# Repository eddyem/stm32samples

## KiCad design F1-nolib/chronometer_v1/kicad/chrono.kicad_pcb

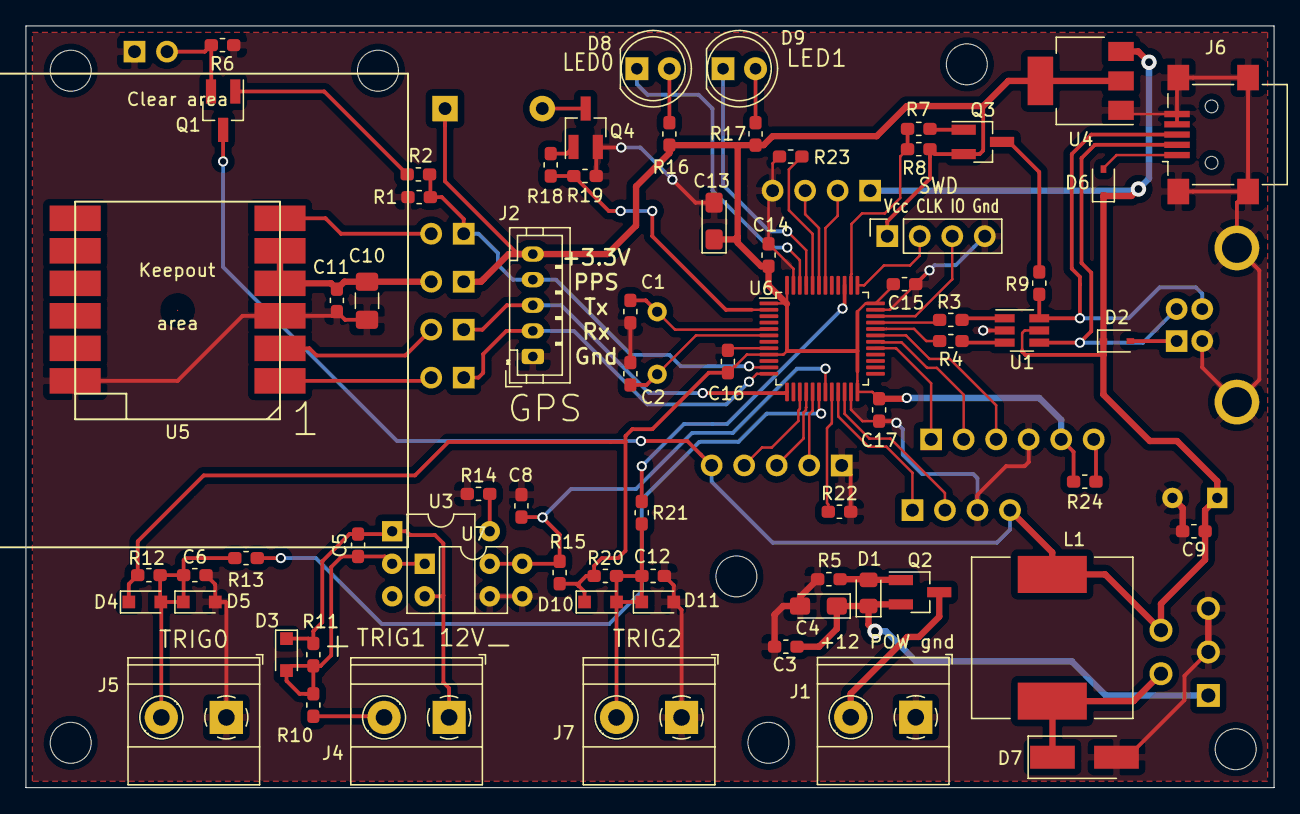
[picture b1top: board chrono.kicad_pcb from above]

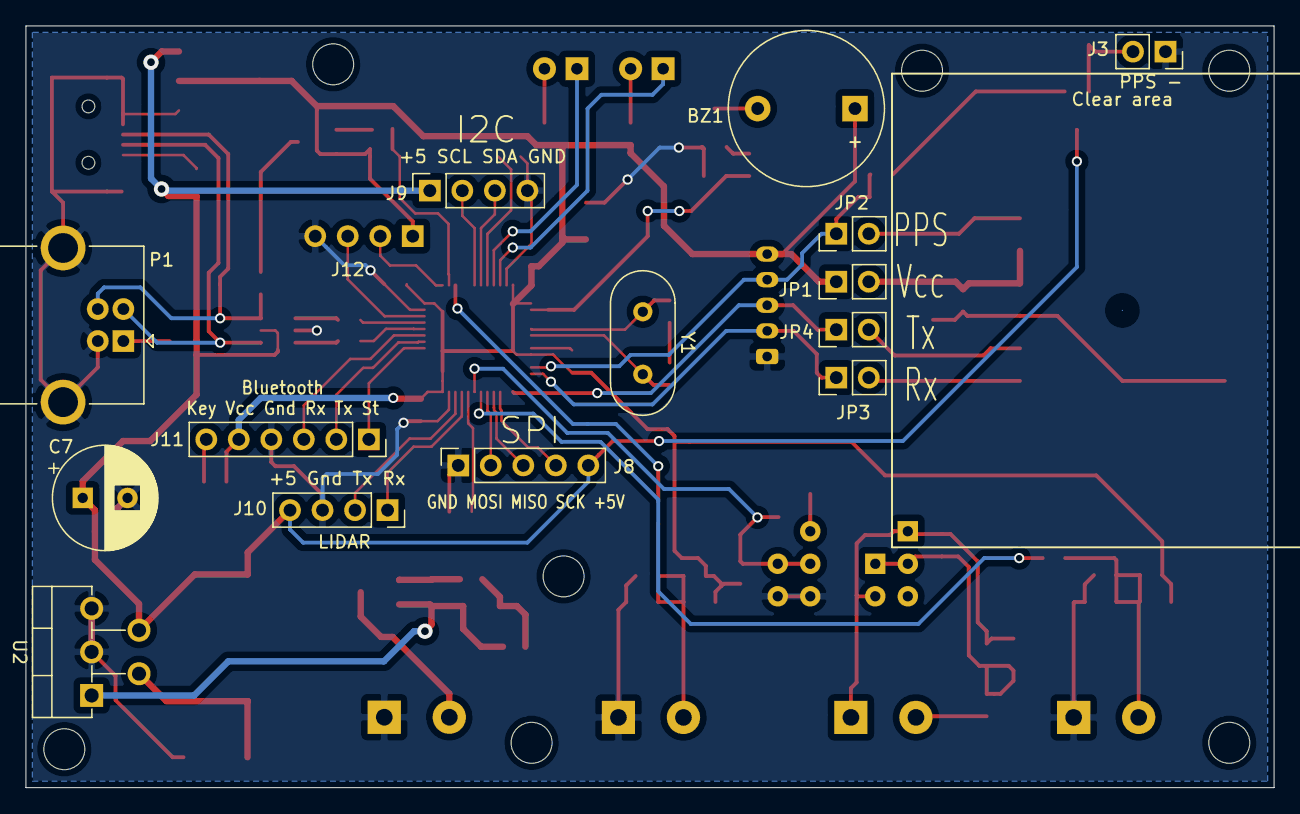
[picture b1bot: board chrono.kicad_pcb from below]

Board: 2 copper layers, 97.5 x 59.5 mm, 83 parts (14 on the bottom side), 60 nets.

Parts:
BZ1: Buzzer 3v3; Buzzer_12x9.5RM7.6
C1, C2: 12; C_0603_1608Metric_Pad1.05x0.95mm_HandSolder
C3, C5, C6, C8, C9, C11, C12, C14, C15, C16, C17: 0.1; C_0603_1608Metric_Pad1.05x0.95mm_HandSolder
C4, C13: 47u; CP_EIA-3216-18_Kemet-A_Pad1.58x1.35mm_HandSolder
C7: 100u; CP_Radial_D8.0mm_P3.50mm
C10: 10u; C_1206_3216Metric_Pad1.42x1.75mm_HandSolder
D1: MM3Z7V5; D_0805_2012Metric_Pad1.15x1.40mm_HandSolder
D2, D6: IN5819; D_SOD-323
D3, D4, D5, D10, D11: 1N5819; D_SOD-323_HandSoldering
D7: B340A; D_SMA_Handsoldering
D8: LED0; LED_D5.0mm
D9: LED1; LED_D5.0mm
J1: Power 12V; TerminalBlock_Phoenix_MKDS-1,5-2-5.08_1x02_P5.08mm_Horizont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
J2: GPS_ext; JST_PH_B5B-PH-K_1x05_P2.00mm_Vertical
J3: PPS; PinSocket_1x02_P2.54mm_Vertical
J4: Ext_trig1; TerminalBlock_Phoenix_MKDS-1,5-2-5.08_1x02_P5.08mm_Horizont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
J5: Ext_trig0; TerminalBlock_Phoenix_MKDS-1,5-2-5.08_1x02_P5.08mm_Horizont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
J6: USB_B_Mini; USB_Mini-B_Lumberg_2486_01_Horizontal
J7: Ext_trig2; TerminalBlock_Phoenix_MKDS-1,5-2-5.08_1x02_P5.08mm_Horizont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
J8: SPI; PinSocket_1x05_P2.54mm_Vertical
J9: I2C1; PinSocket_1x04_P2.54mm_Vertical
J10: LIDAR; PinSocket_1x04_P2.54mm_Vertical
J11: Bluetooth; PinSocket_1x06_P2.54mm_Vertical
J12: SWD; PinSocket_1x04_P2.54mm_Vertical
JP1, JP2, JP3, JP4: Jumper; PinHeader_1x02_P2.54mm_Vertical
L1: 100u; L_12x12mm_H4.5mm
P1: USB_B; USB_B_OST_USB-B1HSxx_Horizontal
Q1: MMBTA42; SOT-23_Handsoldering
Q2: AO3407; SOT-23_Handsoldering
Q3: SI2305; SOT-23_Handsoldering
Q4: IRML2502; SOT-23_Handsoldering
R1, R5, R8, R19, R23: 10k; R_0603_1608Metric_Pad1.05x0.95mm_HandSolder
R2: 2k2; R_0603_1608Metric_Pad1.05x0.95mm_HandSolder
R3, R4: 22; R_0603_1608Metric_Pad1.05x0.95mm_HandSolder
R6, R10, R11, R12, R20: 1k; R_0603_1608Metric_Pad1.05x0.95mm_HandSolder
R7, R18: 510; R_0603_1608Metric_Pad1.05x0.95mm_HandSolder
R9: 1k5; R_0603_1608Metric_Pad1.05x0.95mm_HandSolder
R13, R21: 100; R_0603_1608Metric_Pad1.05x0.95mm_HandSolder
R14, R24: 47k; R_0603_1608Metric_Pad1.05x0.95mm_HandSolder
R15, R16, R17: 220; R_0603_1608Metric_Pad1.05x0.95mm_HandSolder
R22: 100k; R_0603_1608Metric_Pad1.05x0.95mm_HandSolder
U1: USBLC6-2SC6; SOT-23-6_Handsoldering
U2: LM2576-5.0; TO-220-5_P3.4x3.7mm_StaggerEven_Lead3.8mm_Vertical
U3: 4N25; DIP-6_W7.62mm
U4: LM1117-3.3; SOT-223
U5: L80-R
U6: STM32F103C6Tx; LQFP-48_7x7mm_P0.5mm
U7: PC817; DIP-4_W7.62mm
Y1: 8MHz; Crystal_HC49-U_Vertical

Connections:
+3V3: BZ1.1, C13.1, C14.2, C15.2, C16.2, C17.2, D4.1, D10.1, J2.5, J11.5, J12.1, JP1.1, Q3.2, R8.2, R12.2, R15.1, R16.2, R17.2, R20.2, R24.1, U4.2, U4.4, U6.1, U6.9, U6.24, U6.36, U6.48
+5V: C7.1, C9.1, D2.1, D6.1, J8.5, J9.1, J10.4, L1.1, Q1.3, U1.5, U2.4, U4.3
/DM: J6.2, P1.2, U1.4
/DP: J6.3, P1.3, R9.2, U1.6
/LED0: D8.1, U6.46
/LED1: D9.1, U6.45
/MISO: J8.3, U6.16
/MOSI: J8.2, U6.17
/OSC_IN: C1.1, U6.5, Y1.1
/OSC_OUT: C2.1, U6.6, Y1.2
/PPS: J2.4, JP2.1, R1.1, R2.2, U6.11
/SCK: J8.4, U6.15
/SCL: J9.2, U6.42
/SDA: J9.3, U6.43
/SWCLK: J12.2, U6.37
/SWDIO: J12.3, U6.34
/TRIG0: R13.2, U6.18
/TRIG1: C8.1, R15.2, U3.5, U6.19, U7.4
/TRIG2: R21.2, U6.39
/U1Rx: J11.3, U6.31
/U1Tx: J11.2, U6.30
/U2Rx: J10.2, U6.22
/U2Tx: J10.1, U6.21
/U3Rx: J2.3, JP4.1, U6.13
/U3Tx: J2.2, JP3.1, U6.12
/USBDM: R4.2, U6.32
/USBDP: R3.2, U6.33
/USB_PU: R7.2, R8.1, U6.38
/buzzer: R18.2, R19.1, U6.2
GND: C1.2, C2.2, C3.2, C4.2, C6.2, C7.2, C8.2, C9.2, C10.1, C11.1, C12.2, C13.2, C14.1, C15.1, C16.1, C17.1, D5.2, D7.2, D11.2, J1.1, J2.1, J3.1, J5.1, J6.4, J6.5, J6.6, J7.1, J8.1, J9.4, J10.3, J11.4, J12.4, P1.4, P1.5, Q4.2, R1.2, R5.1, R6.1, R14.1, R19.2, R22.2, R23.2, U1.2, U2.3, U2.5, U3.4, U4.1, U5.3, U5.12, U6.8, U6.23, U6.35, U6.47, U7.3
unnamed: BZ1.2, Q4.3
unnamed: C3.1, C4.1, D1.1, Q2.2, U2.1
unnamed: C5.1, D3.2, R10.2, R11.2, U3.2, U7.1
unnamed: C5.2, D3.1, J4.1, R11.1, U3.1, U7.2
unnamed: C6.1, D4.2, D5.1, J5.2, R12.1, R13.1
unnamed: C10.2, C11.2, JP1.2, U5.4, U5.5
unnamed: C12.1, D10.2, D11.1, J7.2, R20.1, R21.1
unnamed: D1.2, Q2.1, R5.2
unnamed: D2.2, P1.1
unnamed: D6.2, J6.1
unnamed: D7.1, L1.2, U2.2
unnamed: D8.2, R16.1
unnamed: D9.2, R17.1
unnamed: J1.2, Q2.3
unnamed: J3.2, Q1.2, R6.2
unnamed: J4.2, R10.1
unnamed: J11.1, U6.29
unnamed: J11.6, R24.2
unnamed: JP2.2, U5.6
unnamed: JP3.2, U5.1
unnamed: JP4.2, U5.2
unnamed: Q1.1, R2.1
unnamed: Q3.1, R7.1
unnamed: Q3.3, R9.1
unnamed: Q4.1, R18.1
unnamed: R3.1, U1.1
unnamed: R4.1, U1.3
unnamed: R14.2, U3.6
unnamed: R22.1, U6.20
unnamed: R23.1, U6.44

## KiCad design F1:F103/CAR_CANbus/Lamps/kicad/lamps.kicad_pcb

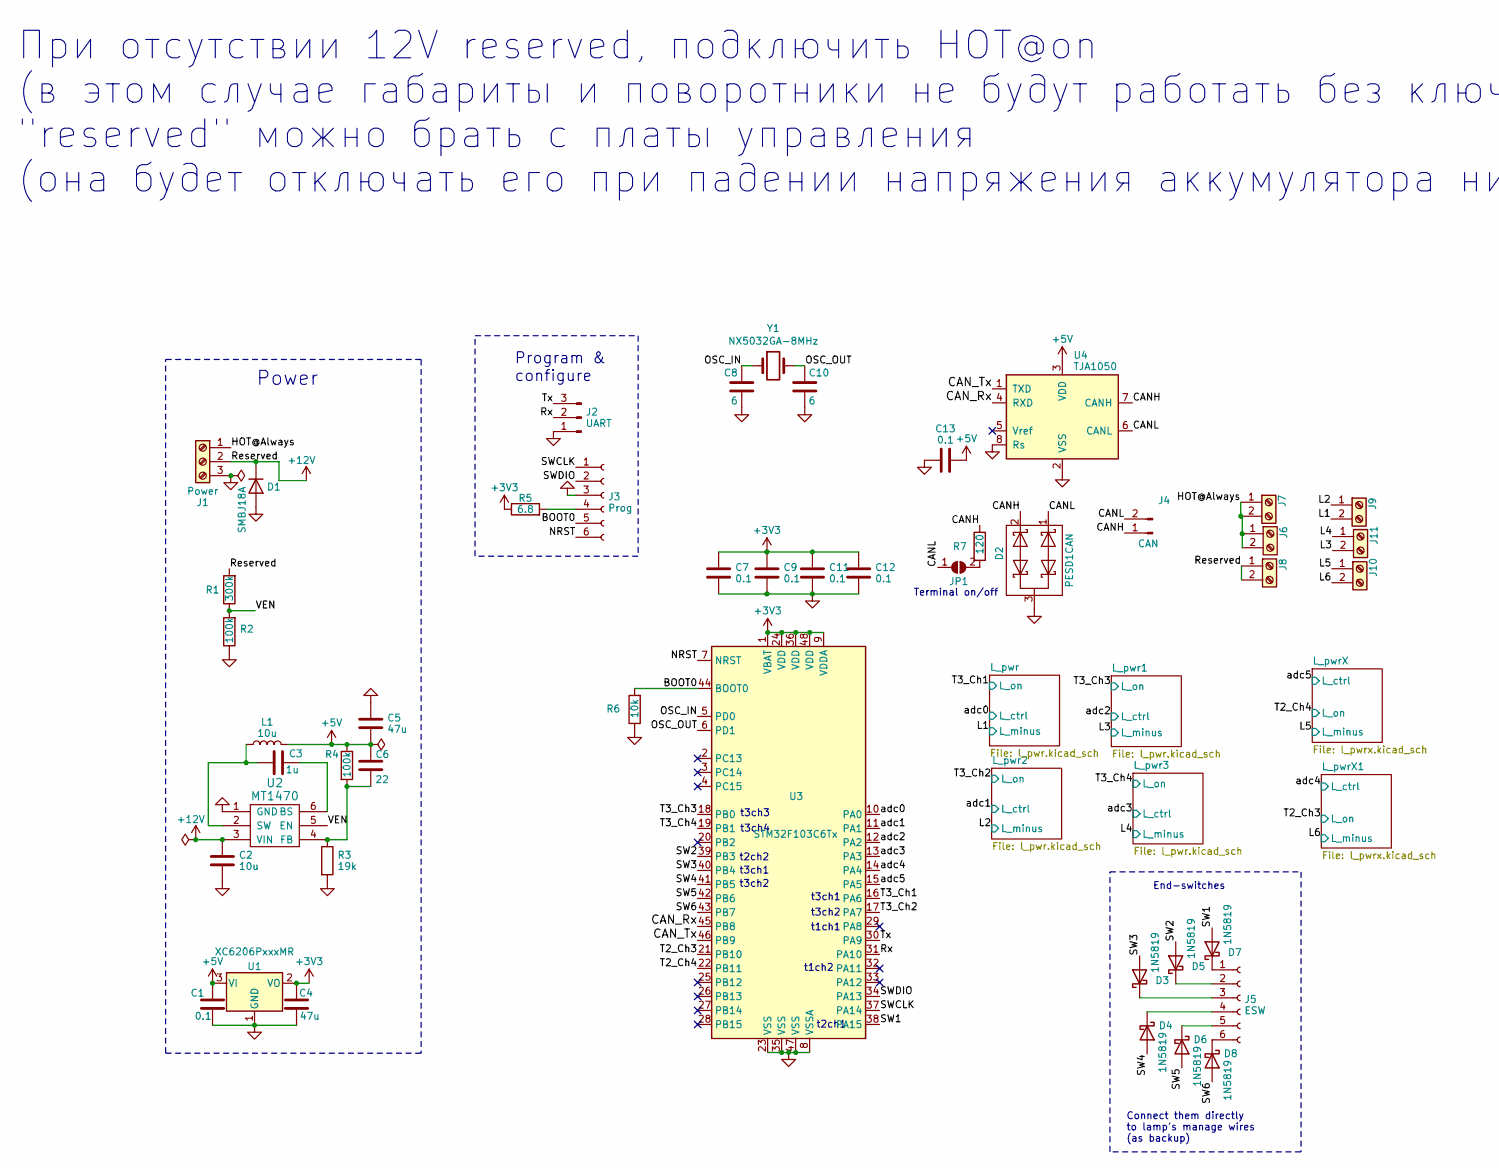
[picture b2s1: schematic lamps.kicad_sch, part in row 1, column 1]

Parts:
C1, C7, C9, C11, C12, C13: 0.1; C_0603_1608Metric_Pad1.08x0.95mm_HandSolder
C2: 10u; C_1206_3216Metric_Pad1.33x1.80mm_HandSolder
C3: 1u; C_1206_3216Metric_Pad1.33x1.80mm_HandSolder
C4: 47u; C_1206_3216Metric
C5: 47u; C_1206_3216Metric_Pad1.33x1.80mm_HandSolder
C6: 22; C_0805_2012Metric_Pad1.18x1.45mm_HandSolder
C8, C10: 6; C_0603_1608Metric_Pad1.08x0.95mm_HandSolder
D1: SMBJ18A; D_SMB_Handsoldering
D2: PESD1CAN; SOT-23
D3, D4, D5, D6, D7, D8: 1N5819; D_SOD-323_HandSoldering
J1: Power; TerminalBlock_Phoenix_MKDS-1,5-3-5.08_1x03_P5.08mm_Horizont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
J2: UART; PinSocket_1x03_P2.54mm_Vertical
J3: Prog; PinSocket_1x06_P1.27mm_Vertical
J4: CAN; JST_PH_B2B-PH-K_1x02_P2.00mm_Vertical
J5: ESW; PinSocket_1x06_P2.54mm_Vertical
J6, J7: ACC; TerminalBlock_Phoenix_MKDS-1,5-2_1x02_P5.00mm_Horizontal
J8: Reserved; TerminalBlock_Phoenix_MKDS-1,5-2_1x02_P5.00mm_Horizontal
J9, J10, J11: Lamp; TerminalBlock_Phoenix_MKDS-1,5-2_1x02_P5.00mm_Horizontal
JP1: Term; SolderJumper-2_P1.3mm_Open_TrianglePad1.0x1.5mm
L1: 10u; cd43
R1: 300k; R_0603_1608Metric_Pad0.98x0.95mm_HandSolder
R2, R4: 100k; R_0603_1608Metric_Pad0.98x0.95mm_HandSolder
R3: 19k; R_0603_1608Metric_Pad0.98x0.95mm_HandSolder
R5: 6.8; R_0603_1608Metric_Pad0.98x0.95mm_HandSolder
R6: 10k; R_0603_1608Metric_Pad0.98x0.95mm_HandSolder
R7: 120; R_1210_3225Metric_Pad1.30x2.65mm_HandSolder
U1: XC6206PxxxMR; SOT-23-3
U2: MT1470; SOT-23-6_Handsoldering
U3: STM32F103C6Tx; LQFP-48_7x7mm_P0.5mm
U4: TJA1050; SOIC-8_3.9x4.9mm_P1.27mm
Y1: NX5032GA-8MHz; Crystal_SMD_5032-2Pin_5.0x3.2mm

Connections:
+3V3: C4.1, C7.1, C9.1, C11.1, C12.1, R5.1, U1.2 (VO), U3.1 (VBAT), U3.9 (VDDA), U3.24 (VDD), U3.36 (VDD), U3.48 (VDD)
+5V: C1.1, C5.1, C6.1, C13.2, L1.2, R4.1, U1.3 (VI), U4.3 (VDD)
+12V: C2.2, D1.1 (K), J1.2, J8.1, J8.2, R1.2, U2.3 (VIN)
/BOOT0: J3.5, R6.2, U3.44 (BOOT0)
/CANH: D2.2 (K), J4.1, R7.1, U4.7 (CANH)
/CANL: D2.1 (K), J4.2, JP1.1 (A), U4.6 (CANL)
/CAN_Rx: U3.45 (PB8), U4.4 (RXD)
/CAN_Tx: U3.46 (PB9), U4.1 (TXD)
/HOT@Always: J1.1, J6.1, J6.2, J7.1, J7.2
/L1: J9.2; also elsewhere on the board
/L2: J9.1; also elsewhere on the board
/L3: J11.2; also elsewhere on the board
/L4: J11.1; also elsewhere on the board
/L5: J10.1; also elsewhere on the board
/L6: J10.2; also elsewhere on the board
/NRST: J3.6, U3.7 (NRST)
/OSC_IN: C8.1, U3.5 (PD0), Y1.1
/OSC_OUT: C10.1, U3.6 (PD1), Y1.2
/Rx: J2.2, U3.31 (PA10)
/SW1: D7.2 (A), U3.38 (PA15)
/SW2: D5.2 (A), U3.39 (PB3)
/SW3: D3.2 (A), U3.40 (PB4)
/SW4: D4.2 (A), U3.41 (PB5)
/SW5: D6.2 (A), U3.42 (PB6)
/SW6: D8.2 (A), U3.43 (PB7)
/SWCLK: J3.1, U3.37 (PA14)
/SWDIO: J3.2, U3.34 (PA13)
/T2_Ch3: U3.21 (PB10); also elsewhere on the board
/T2_Ch4: U3.22 (PB11); also elsewhere on the board
/T3_Ch1: U3.16 (PA6); also elsewhere on the board
/T3_Ch2: U3.17 (PA7); also elsewhere on the board
/T3_Ch3: U3.18 (PB0); also elsewhere on the board
/T3_Ch4: U3.19 (PB1); also elsewhere on the board
/Tx: J2.3, U3.30 (PA9)
/VEN: R1.1, R2.2, U2.5 (EN)
/adc0: U3.10 (PA0); also elsewhere on the board
/adc1: U3.11 (PA1); also elsewhere on the board
/adc2: U3.12 (PA2); also elsewhere on the board
/adc3: U3.13 (PA3); also elsewhere on the board
/adc4: U3.14 (PA4); also elsewhere on the board
/adc5: U3.15 (PA5); also elsewhere on the board
GND: C1.2, C2.1, C4.2, C5.2, C7.2, C8.2, C9.2, C10.2, C11.2, C12.2, C13.1, D1.2 (A), D2.3 (O), J1.3, J2.1, J3.3, R2.1, R3.2, R6.1, U1.1 (GND), U2.1 (GND), U3.8 (VSSA), U3.23 (VSS), U3.35 (VSS), U3.47 (VSS), U4.2 (VSS), U4.8 (Rs); also elsewhere on the board
unnamed: D3.1 (K), J5.3
unnamed: D4.1 (K), J5.4
unnamed: D5.1 (K), J5.2
unnamed: D6.1 (K), J5.5
unnamed: D7.1 (K), J5.1
unnamed: D8.1 (K), J5.6
unnamed: J3.4, R5.2
unnamed: JP1.2 (B), R7.2
unnamed: C3.2, U2.6 (BS)
unnamed: C6.2, R3.1, R4.2, U2.4 (FB)
unnamed: C3.1, L1.1, U2.2 (SW)

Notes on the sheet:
t3ch4
При отсутствии 12V reserved, подключить HOT@on (в этом случае габариты и поворотники не будут работать без ключа!) "reserved" можно брать с платы управления (она будет отключать его при падении напряжения аккумулятора ниже 10В).
t3ch2
Connect them directly to lamp's manage wires (as backup)
t1ch2
t2ch2
t2ch1
Terminal on/off
Program & configure
t3ch3
End-switches
t3ch1
Power
t1ch1

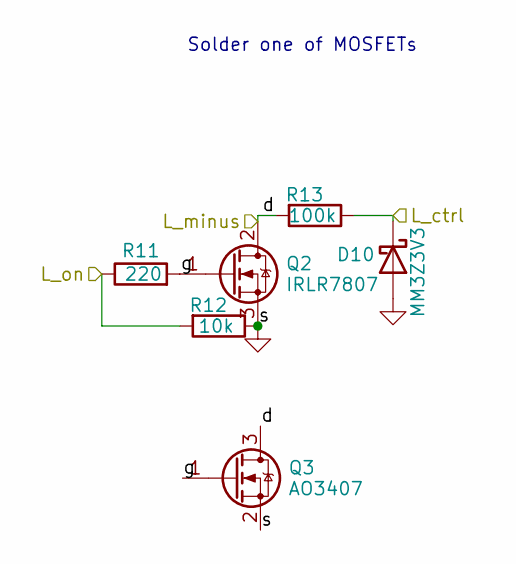
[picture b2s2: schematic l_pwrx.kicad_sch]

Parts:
D10: MM3Z3V3; D_0805_2012Metric_Pad1.15x1.40mm_HandSolder
Q2: IRLR7807; TO-252-3_TabPin2
Q3: AO3407; SOT-23_Handsoldering
R11: 220; R_0603_1608Metric_Pad0.98x0.95mm_HandSolder
R12: 10k; R_0603_1608Metric_Pad0.98x0.95mm_HandSolder
R13: 100k; R_0603_1608Metric_Pad0.98x0.95mm_HandSolder

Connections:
/L5: Q2.2 (D), Q3.3 (D), R13.2; also elsewhere on the board
/L_pwrX/g: Q2.1 (G), Q3.1 (G), R11.2
/T2_Ch4: R11.1, R12.2; also elsewhere on the board
/adc5: D10.1 (K), R13.1; also elsewhere on the board
GND: D10.2 (A), Q2.3 (S), Q3.2 (S), R12.1; also elsewhere on the board

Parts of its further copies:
D14: MM3Z3V3; D_0805_2012Metric_Pad1.15x1.40mm_HandSolder
Q7: IRLR7807; TO-252-3_TabPin2
Q8: AO3407; SOT-23_Handsoldering
R23: 220; R_0603_1608Metric_Pad0.98x0.95mm_HandSolder
R24: 10k; R_0603_1608Metric_Pad0.98x0.95mm_HandSolder
R25: 100k; R_0603_1608Metric_Pad0.98x0.95mm_HandSolder

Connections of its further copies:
/L6: Q7.2 (D), Q8.3 (D), R25.2; also elsewhere on the board
/L_pwrX1/g: Q7.1 (G), Q8.1 (G), R23.2
/T2_Ch3: R23.1, R24.2; also elsewhere on the board
/adc4: D14.1 (K), R25.1; also elsewhere on the board
GND: D14.2 (A), Q7.3 (S), Q8.2 (S), R24.1; also elsewhere on the board

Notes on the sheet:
Solder one of MOSFETs

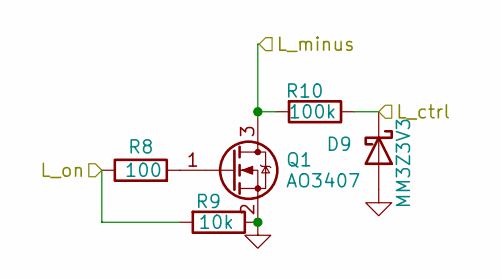
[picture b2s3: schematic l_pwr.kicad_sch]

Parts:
D9: MM3Z3V3; D_0805_2012Metric_Pad1.15x1.40mm_HandSolder
Q1: AO3407; SOT-23_Handsoldering
R8: 100; R_0603_1608Metric_Pad0.98x0.95mm_HandSolder
R9: 10k; R_0603_1608Metric_Pad0.98x0.95mm_HandSolder
R10: 100k; R_0603_1608Metric_Pad0.98x0.95mm_HandSolder

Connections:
/L1: Q1.3 (D), R10.2; also elsewhere on the board
/T3_Ch1: R8.1, R9.2; also elsewhere on the board
/adc0: D9.1 (K), R10.1; also elsewhere on the board
GND: D9.2 (A), Q1.2 (S), R9.1; also elsewhere on the board
unnamed: Q1.1 (G), R8.2

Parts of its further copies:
D11, D12, D13: MM3Z3V3; D_0805_2012Metric_Pad1.15x1.40mm_HandSolder
Q4, Q5, Q6: AO3407; SOT-23_Handsoldering
R14, R17, R20: 100; R_0603_1608Metric_Pad0.98x0.95mm_HandSolder
R15, R18, R21: 10k; R_0603_1608Metric_Pad0.98x0.95mm_HandSolder
R16, R19, R22: 100k; R_0603_1608Metric_Pad0.98x0.95mm_HandSolder

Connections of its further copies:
/L2: Q5.3 (D), R19.2; also elsewhere on the board
/L3: Q4.3 (D), R16.2; also elsewhere on the board
/L4: Q6.3 (D), R22.2; also elsewhere on the board
/T3_Ch2: R17.1, R18.2; also elsewhere on the board
/T3_Ch3: R14.1, R15.2; also elsewhere on the board
/T3_Ch4: R20.1, R21.2; also elsewhere on the board
/adc1: D12.1 (K), R19.1; also elsewhere on the board
/adc2: D11.1 (K), R16.1; also elsewhere on the board
/adc3: D13.1 (K), R22.1; also elsewhere on the board
GND: D11.2 (A), D12.2 (A), D13.2 (A), Q4.2 (S), Q5.2 (S), Q6.2 (S), R15.1, R18.1, R21.1; also elsewhere on the board
unnamed: Q4.1 (G), R14.2
unnamed: Q5.1 (G), R17.2
unnamed: Q6.1 (G), R20.2

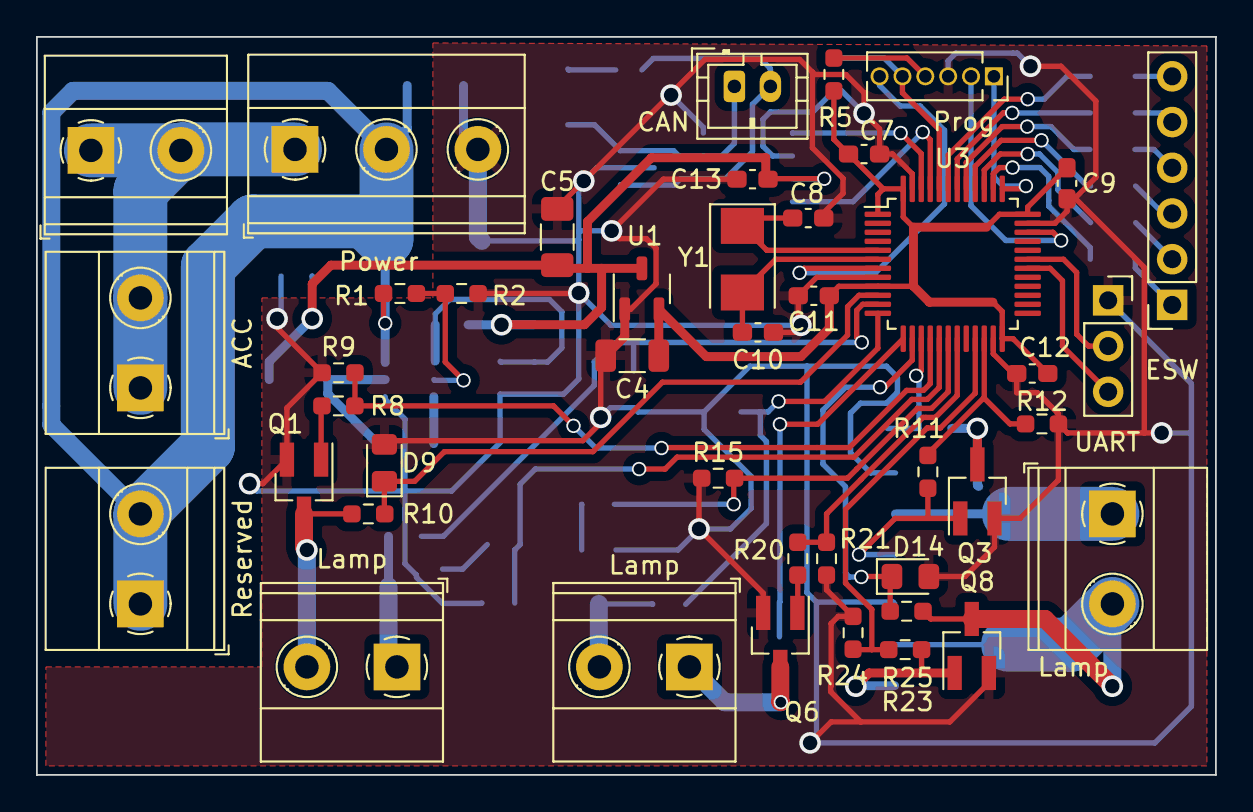
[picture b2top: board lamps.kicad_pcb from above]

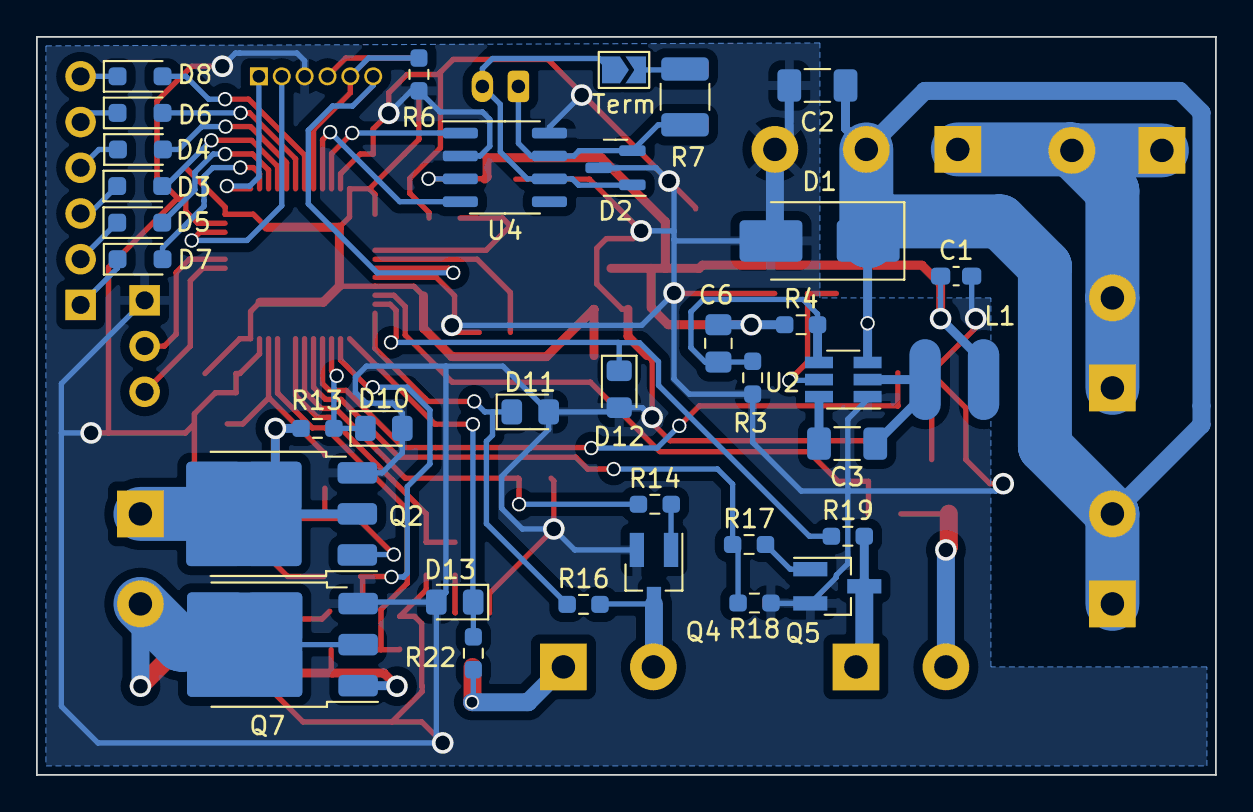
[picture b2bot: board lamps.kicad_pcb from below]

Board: 2 copper layers, 65.5 x 41.0 mm, 78 parts (35 on the bottom side), 59 nets.

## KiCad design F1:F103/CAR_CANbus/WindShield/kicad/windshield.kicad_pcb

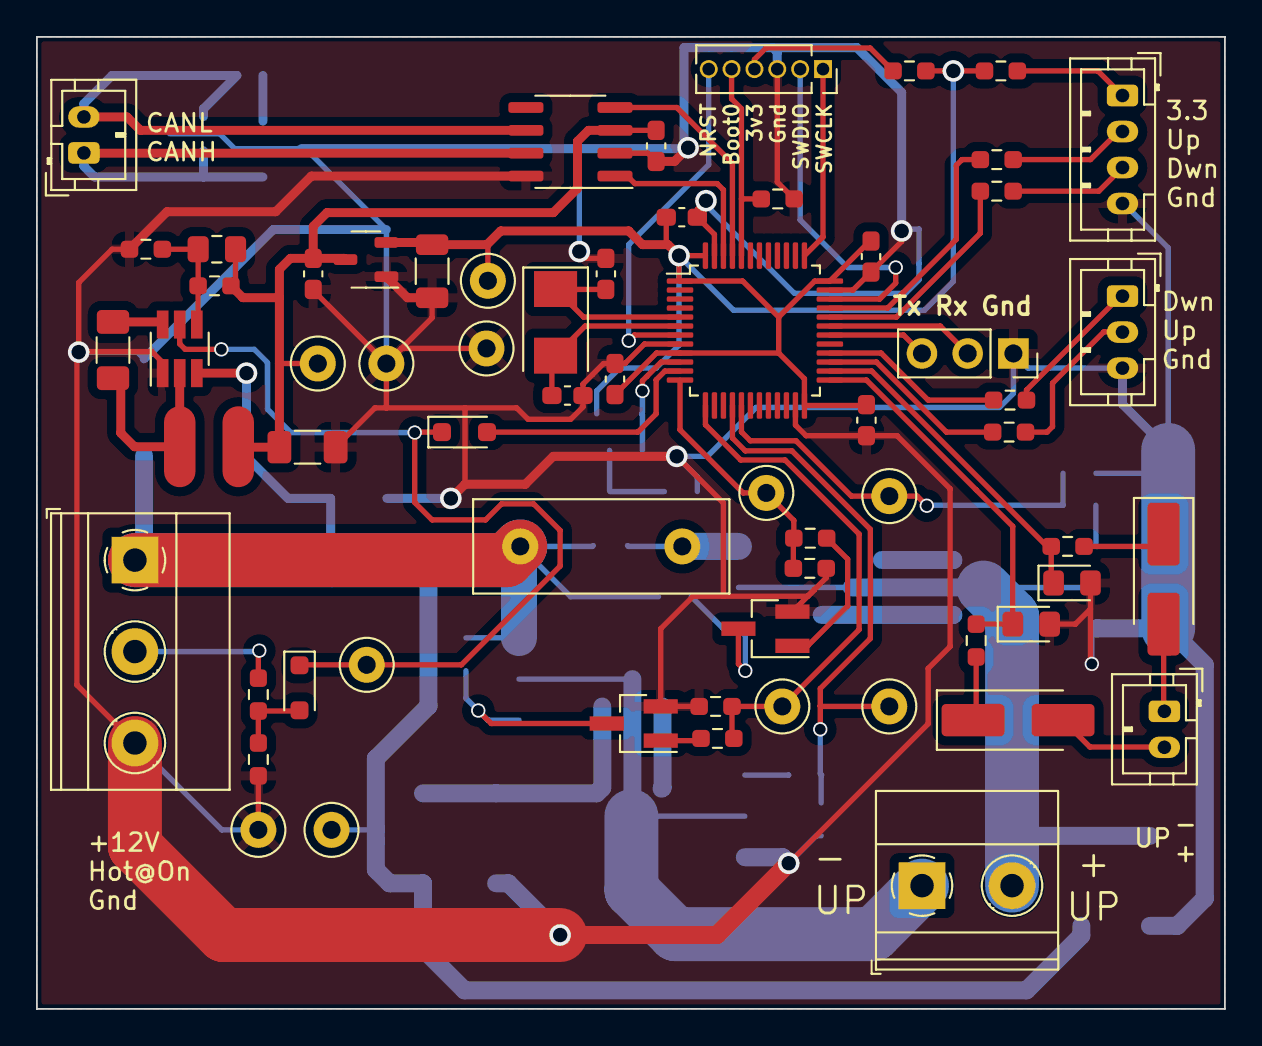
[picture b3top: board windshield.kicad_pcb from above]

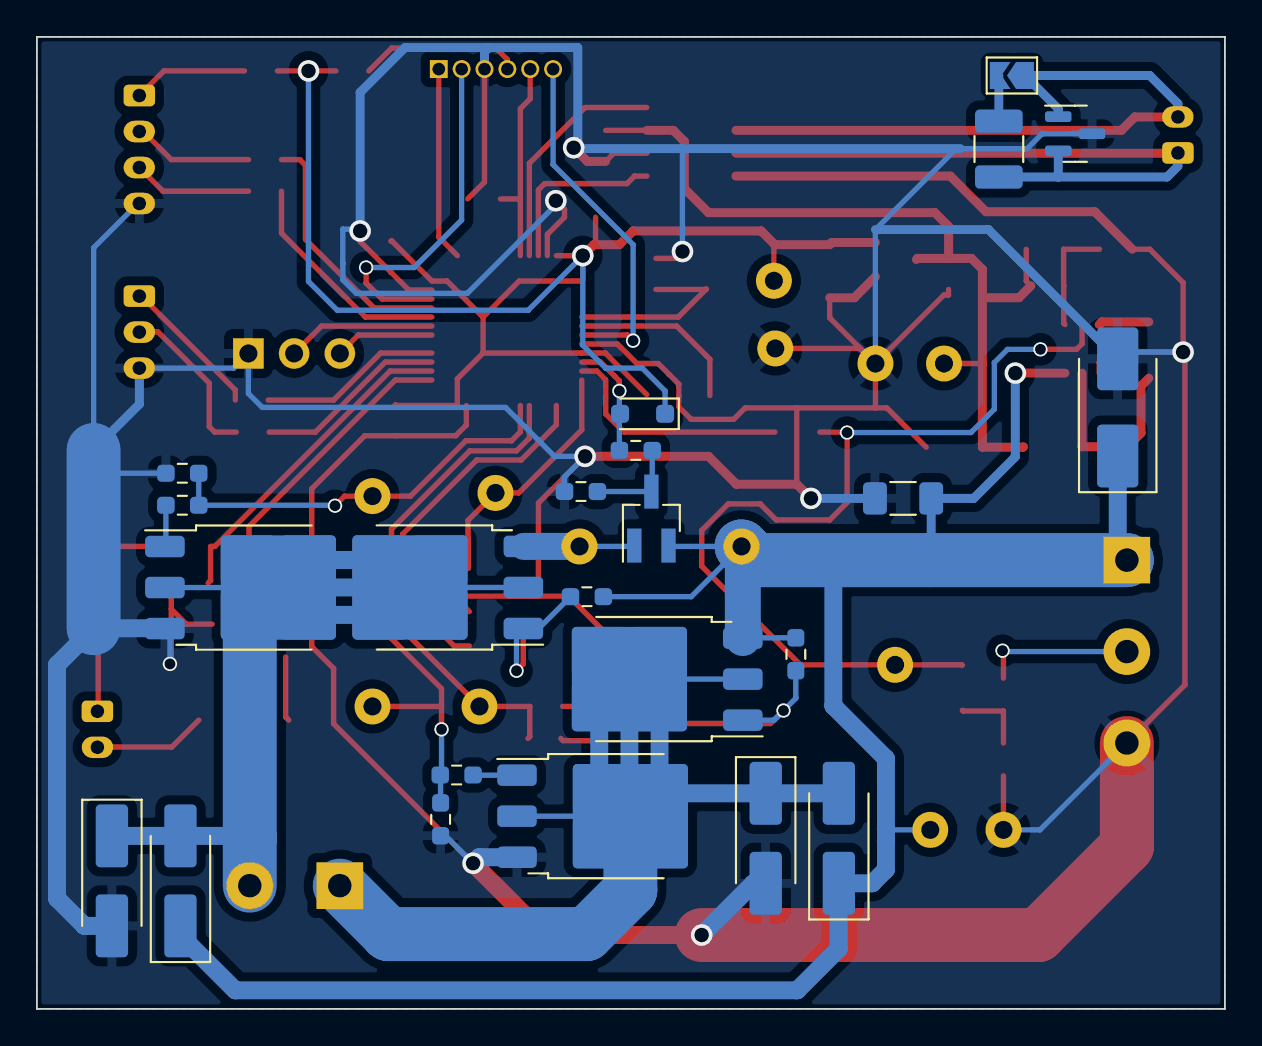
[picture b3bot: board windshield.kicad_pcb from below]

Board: 2 copper layers, 66.0 x 54.0 mm, 86 parts (23 on the bottom side), 55 nets.

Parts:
C1, C7, C9, C11, C12, C13: 0.1; C_0603_1608Metric_Pad1.08x0.95mm_HandSolder
C2: 10u; C_1206_3216Metric_Pad1.33x1.80mm_HandSolder
C3: 1u; C_1206_3216Metric_Pad1.33x1.80mm_HandSolder
C4: 47u; C_1206_3216Metric
C5: 47u; C_1206_3216Metric_Pad1.33x1.80mm_HandSolder
C6: 22; C_0805_2012Metric_Pad1.18x1.45mm_HandSolder
C8, C10: 6; C_0603_1608Metric_Pad1.08x0.95mm_HandSolder
D1, D2, D8: 1N5819; D_SOD-323_HandSoldering
D3: SMBJ18A; D_SMB_Handsoldering
D4, D5, D9, D10, D11, D12: 1N4007; D_SMA_Handsoldering
D6, D7: MM3Z3V3; D_0805_2012Metric_Pad1.15x1.40mm_HandSolder
D13: PESD1CAN; SOT-23
J1: Power; TerminalBlock_Phoenix_MKDS-1,5-3-5.08_1x03_P5.08mm_Horizont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
J2: Hall; JST_PH_B4B-PH-K_1x04_P2.00mm_Vertical
J3: Buttons; JST_PH_B3B-PH-K_1x03_P2.00mm_Vertical
J4: UART; PinSocket_1x03_P2.54mm_Vertical
J5: Prog; PinSocket_1x06_P1.27mm_Vertical
J6: EXT_MOT; JST_PH_B2B-PH-K_1x02_P2.00mm_Vertical
J7: Motor; TerminalBlock_Phoenix_MKDS-1,5-2_1x02_P5.00mm_Horizontal
J8: CAN; JST_PH_B2B-PH-K_1x02_P2.00mm_Vertical
JP1: Term; SolderJumper-2_P1.3mm_Open_TrianglePad1.0x1.5mm
L1: 10u; cd43
Q1, Q6: 2N7002; SOT-23_Handsoldering
Q2, Q4: AOD4185; TO-252-3_TabPin2
Q3, Q5: IRLR7807; TO-252-3_TabPin2
R1: 300k; R_0603_1608Metric_Pad0.98x0.95mm_HandSolder
R2, R7: 100k; R_0603_1608Metric_Pad0.98x0.95mm_HandSolder
R3: 47; R_0603_1608Metric_Pad0.98x0.95mm_HandSolder
R4, R5, R8, R9, R15, R16, R25: 100; R_0603_1608Metric_Pad0.98x0.95mm_HandSolder
R6: 19k; R_0603_1608Metric_Pad0.98x0.95mm_HandSolder
R10: 6.8; R_0603_1608Metric_Pad0.98x0.95mm_HandSolder
R11, R17, R19, R22, R23, R26, R27: 10k; R_0603_1608Metric_Pad0.98x0.95mm_HandSolder
R12, R13: 1k; R_0603_1608Metric_Pad0.98x0.95mm_HandSolder
R14: 330; R_0603_1608Metric_Pad0.98x0.95mm_HandSolder
R18, R24: 220; R_0603_1608Metric_Pad0.98x0.95mm_HandSolder
R20: 0.05; R_Box_L14.0mm_W5.0mm_P9.00mm
R21: 120; R_1210_3225Metric_Pad1.30x2.65mm_HandSolder
TP1, TP6, TP7: Gnd; TestPoint_Loop_D1.80mm_Drill1.0mm_Beaded
TP2: Ven; TestPoint_Loop_D1.80mm_Drill1.0mm_Beaded
TP3: 12V; TestPoint_Loop_D1.80mm_Drill1.0mm_Beaded
TP4: 5V; TestPoint_Loop_D1.80mm_Drill1.0mm_Beaded
TP5: 3V3; TestPoint_Loop_D1.80mm_Drill1.0mm_Beaded
TP8: L+; TestPoint_Loop_D1.80mm_Drill1.0mm_Beaded
TP9: L-; TestPoint_Loop_D1.80mm_Drill1.0mm_Beaded
TP10: R+; TestPoint_Loop_D1.80mm_Drill1.0mm_Beaded
TP11: R-; TestPoint_Loop_D1.80mm_Drill1.0mm_Beaded
U1: XC6206PxxxMR; SOT-23-3
U2: MT1470; SOT-23-6_Handsoldering
U3: STM32F103C6Tx; LQFP-48_7x7mm_P0.5mm
U4: ZXCT1009; SOT-23_Handsoldering
U5: TJA1050; SOIC-8_3.9x4.9mm_P1.27mm
Y1: NX5032GA-8MHz; Crystal_SMD_5032-2Pin_5.0x3.2mm

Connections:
+3V3: C4.1, C7.1, C9.1, C11.1, C12.1, D8.1 (K), R3.2, R10.1, TP5.1, U1.2 (VO), U3.1 (VBAT), U3.9 (VDDA), U3.24 (VDD), U3.36 (VDD), U3.48 (VDD)
+5V: C1.1, C5.1, C6.1, C13.2, L1.2, R7.1, TP4.1, U1.3 (VI), U5.3 (VDD)
+12V: C2.2, D3.1 (K), D10.1 (K), D11.1 (K), J1.1, Q4.3 (S), R17.2, R20.1, R23.2, TP3.1, U2.3 (VIN), U4.2 (+)
/BOOT0: J5.5, R11.2, U3.44 (BOOT0)
/CANH: D13.2 (K), J8.1, R21.1, U5.7 (CANH)
/CANL: D13.1 (K), J8.2, JP1.1 (A), U5.6 (CANL)
/CAN_Rx: U3.45 (PB8), U5.4 (RXD)
/CAN_Tx: U3.46 (PB9), U5.1 (TXD)
/DOWN_BTN: R8.2, U3.28 (PB15)
/DOWN_DIR: D7.1 (K), R13.1, U3.26 (PB13)
/DOWN_SW: R5.2, U3.32 (PA11)
/HOT@On: J1.2, R1.2
/L_DOWN: R18.1, R19.2, TP9.1, U3.17 (PA7)
/L_UP: R16.1, R26.2, TP8.1, U3.12 (PA2)
/NRST: J5.6, U3.7 (NRST)
/OSC_IN: C8.1, U3.5 (PD0), Y1.1
/OSC_OUT: C10.1, U3.6 (PD1), Y1.2
/Power_EN: D2.2 (A), U3.11 (PA1)
/R_DOWN: R22.1, R24.1, TP11.1, U3.16 (PA6)
/R_UP: R25.1, R27.1, TP10.1, U3.13 (PA3)
/Rx: J4.2, U3.31 (PA10)
/SWCLK: J5.1, U3.37 (PA14)
/SWDIO: J5.2, U3.34 (PA13)
/Tx: J4.3, U3.30 (PA9)
/UP_BTN: R9.2, U3.27 (PB14)
/UP_DIR: D6.1 (K), R12.1, U3.25 (PB12)
/UP_SW: R4.2, U3.33 (PA12)
/VEN: D1.1 (K), D2.1 (K), TP2.1, U2.5 (EN)
/Vsen: D8.2 (A), R14.2, U3.10 (PA0)
GND: C1.2, C2.1, C4.2, C5.2, C7.2, C8.2, C9.2, C10.2, C11.2, C12.2, C13.1, D3.2 (A), D6.2 (A), D7.2 (A), D9.2 (A), D12.2 (A), D13.3 (O), J1.3, J2.4, J3.3, J4.1, J5.3, Q1.2 (S), Q3.3 (S), Q5.3 (S), Q6.2 (S), R2.1, R6.2, R11.1, R15.2, R19.1, R22.2, R26.1, R27.2, TP1.1, TP6.1, TP7.1, U1.1 (GND), U2.1 (GND), U3.8 (VSSA), U3.23 (VSS), U3.35 (VSS), U3.47 (VSS), U5.2 (VSS), U5.8 (Rs)
unnamed: D1.2 (A), R1.1, R2.2
unnamed: D4.2 (A), J6.2
unnamed: D4.1 (K), R12.2
unnamed: D5.2 (A), J6.1
unnamed: D5.1 (K), R13.2
unnamed: D9.1 (K), D10.2 (A), J7.2, Q2.2 (D), Q3.2 (D)
unnamed: D11.2 (A), D12.1 (K), J7.1, Q4.2 (D), Q5.2 (D)
unnamed: J2.1, R3.1
unnamed: J2.2, R4.1
unnamed: J2.3, R5.1
unnamed: J3.1, R8.1
unnamed: J3.2, R9.1
unnamed: J5.4, R10.2
unnamed: JP1.2 (B), R21.2
unnamed: Q1.3 (D), Q2.1 (G), R17.1
unnamed: Q1.1 (G), R16.2
unnamed: Q2.3 (S), R20.2, U4.1 (-)
unnamed: Q3.1 (G), R18.2
unnamed: Q4.1 (G), Q6.3 (D), R23.1
unnamed: Q5.1 (G), R24.2
unnamed: Q6.1 (G), R25.2
unnamed: C3.2, U2.6 (BS)
unnamed: C6.2, R6.1, R7.2, U2.4 (FB)
unnamed: C3.1, L1.1, U2.2 (SW)
unnamed: R14.1, R15.1, U4.3 (sense)
